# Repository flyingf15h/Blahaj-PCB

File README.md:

# Blahaj-PCB
cute blahaj shaped pcb on KiCAD

masterials
- x6 LED
- x6 resistor 220ohm
- x3 CR2032 battery cell and batteries

axolotl

pcb view

3d view

schematic

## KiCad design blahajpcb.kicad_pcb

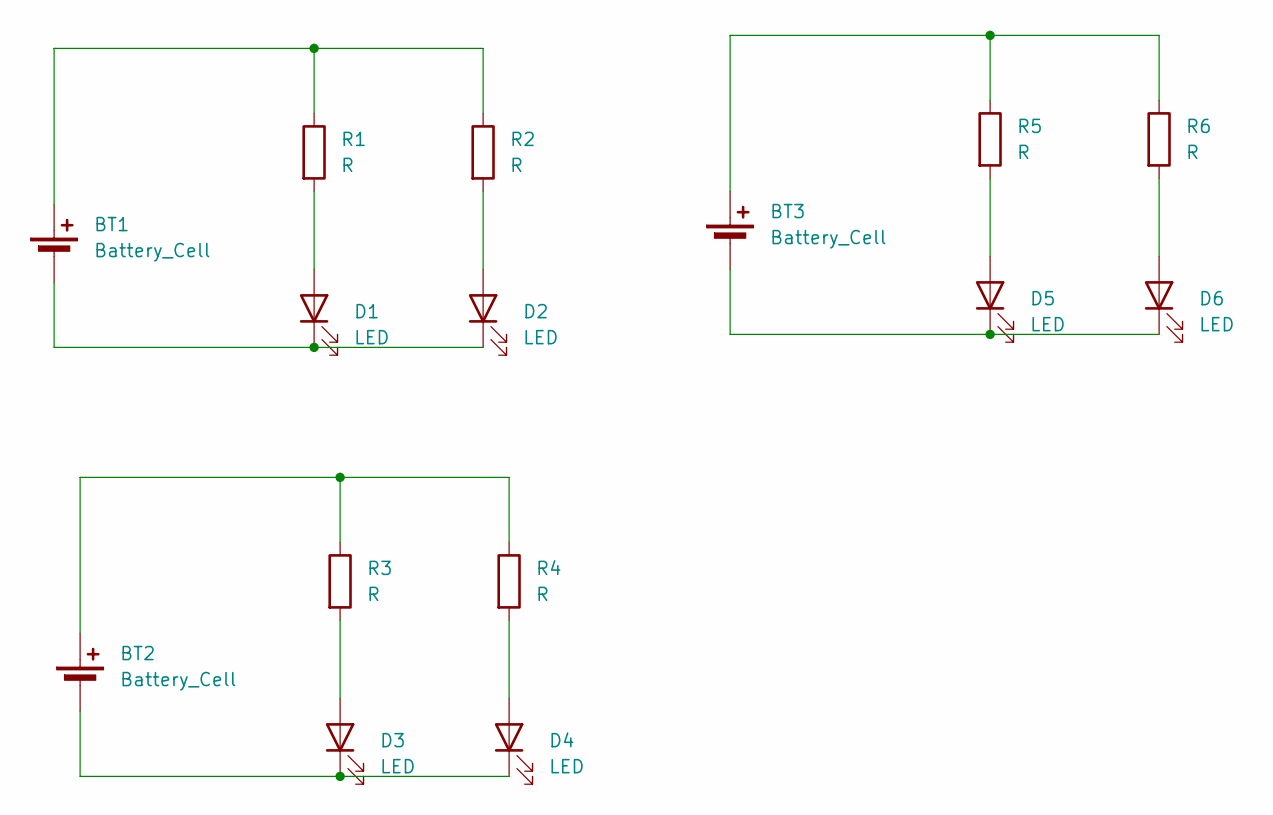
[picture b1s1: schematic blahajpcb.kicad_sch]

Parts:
BT1, BT2, BT3: Battery_Cell; BatteryHolder_Keystone_3034_1x20mm
D1, D2, D3, D4, D5, D6: LED; LED_D5.0mm
R1, R2, R3, R4, R5, R6: R; R_Axial_DIN0207_L6.3mm_D2.5mm_P7.62mm_Horizontal

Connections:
unnamed: BT1.1 (+), R1.1, R2.1
unnamed: BT1.2 (-), D1.1 (K), D2.1 (K)
unnamed: BT2.1 (+), R3.1, R4.1
unnamed: BT2.2 (-), D3.1 (K), D4.1 (K)
unnamed: BT3.1 (+), R5.1, R6.1
unnamed: BT3.2 (-), D5.1 (K), D6.1 (K)
unnamed: D1.2 (A), R1.2
unnamed: D2.2 (A), R2.2
unnamed: D3.2 (A), R3.2
unnamed: D4.2 (A), R4.2
unnamed: D5.2 (A), R5.2
unnamed: D6.2 (A), R6.2

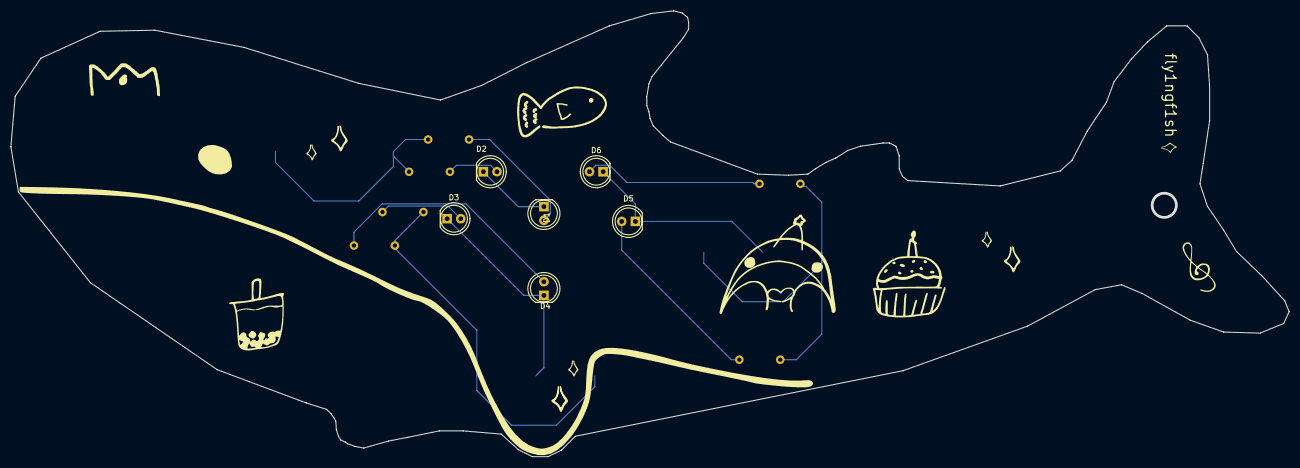
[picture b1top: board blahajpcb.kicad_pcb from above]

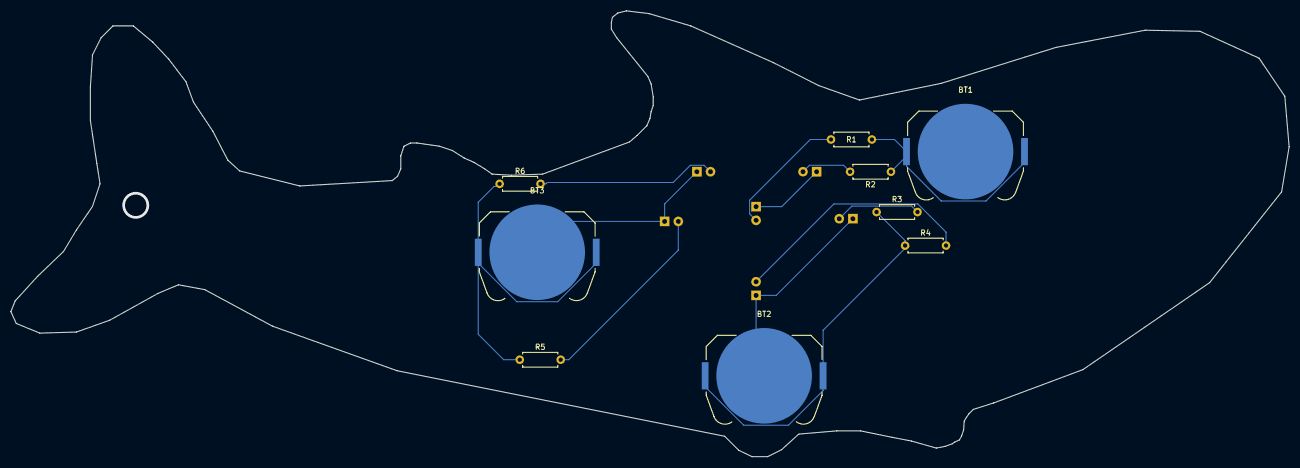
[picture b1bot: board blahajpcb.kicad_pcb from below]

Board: 2 copper layers, 238.0 x 83.0 mm, 15 parts (9 on the bottom side), 12 nets.
